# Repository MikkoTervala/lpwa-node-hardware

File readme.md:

# LPWA Node Hardware

Low power LTE Cat M / NB IoT cellular network temperature and humidity logger.

## Design Overview

The design is based on a combination of the ESP32-C3 and the SIMCom SIM7080G. An ESP32 family microcontroller was chosen as it offers good compatibility with ESPHome firmware generation tools, making the board more broadly usable for home automation purposes. In its intended use, the WiFi and Bluetooth functions will not be used. The purpose of the microcontroller is to gather temperature and humidity readings and transmit them to a server over a cellular connection using the SIM7080 modem.

## Views and Schematics

- [Schematic and board layout](https://kicanvas.org/?repo=https%3A%2F%2Fgithub.com%2FMikkoTervala%2Flpwa-node-hardware%2Ftree%2Fmain%2Fkicad)
- [Interactive 3D view](https://3dviewer.net/index.html#model=https://raw.githubusercontent.com/MikkoTervala/lpwa-node-hardware/main/kicad/release%20a/lpwa-node.step)

## Remarks

The 3.0V regulator is selected with low quiescent current as the top priority, and it cannot sustain enough current to the ESP32-C3 in WiFi operation. Replace the regulator with TLV75730PDBVR before enabling WiFi.

Maximum allowed battery voltage for the system is 4.8V. Do not use lithium 1.5V batteries as their open circuit voltage exceeds limits of this design. Stick to NiMH and alkaline.

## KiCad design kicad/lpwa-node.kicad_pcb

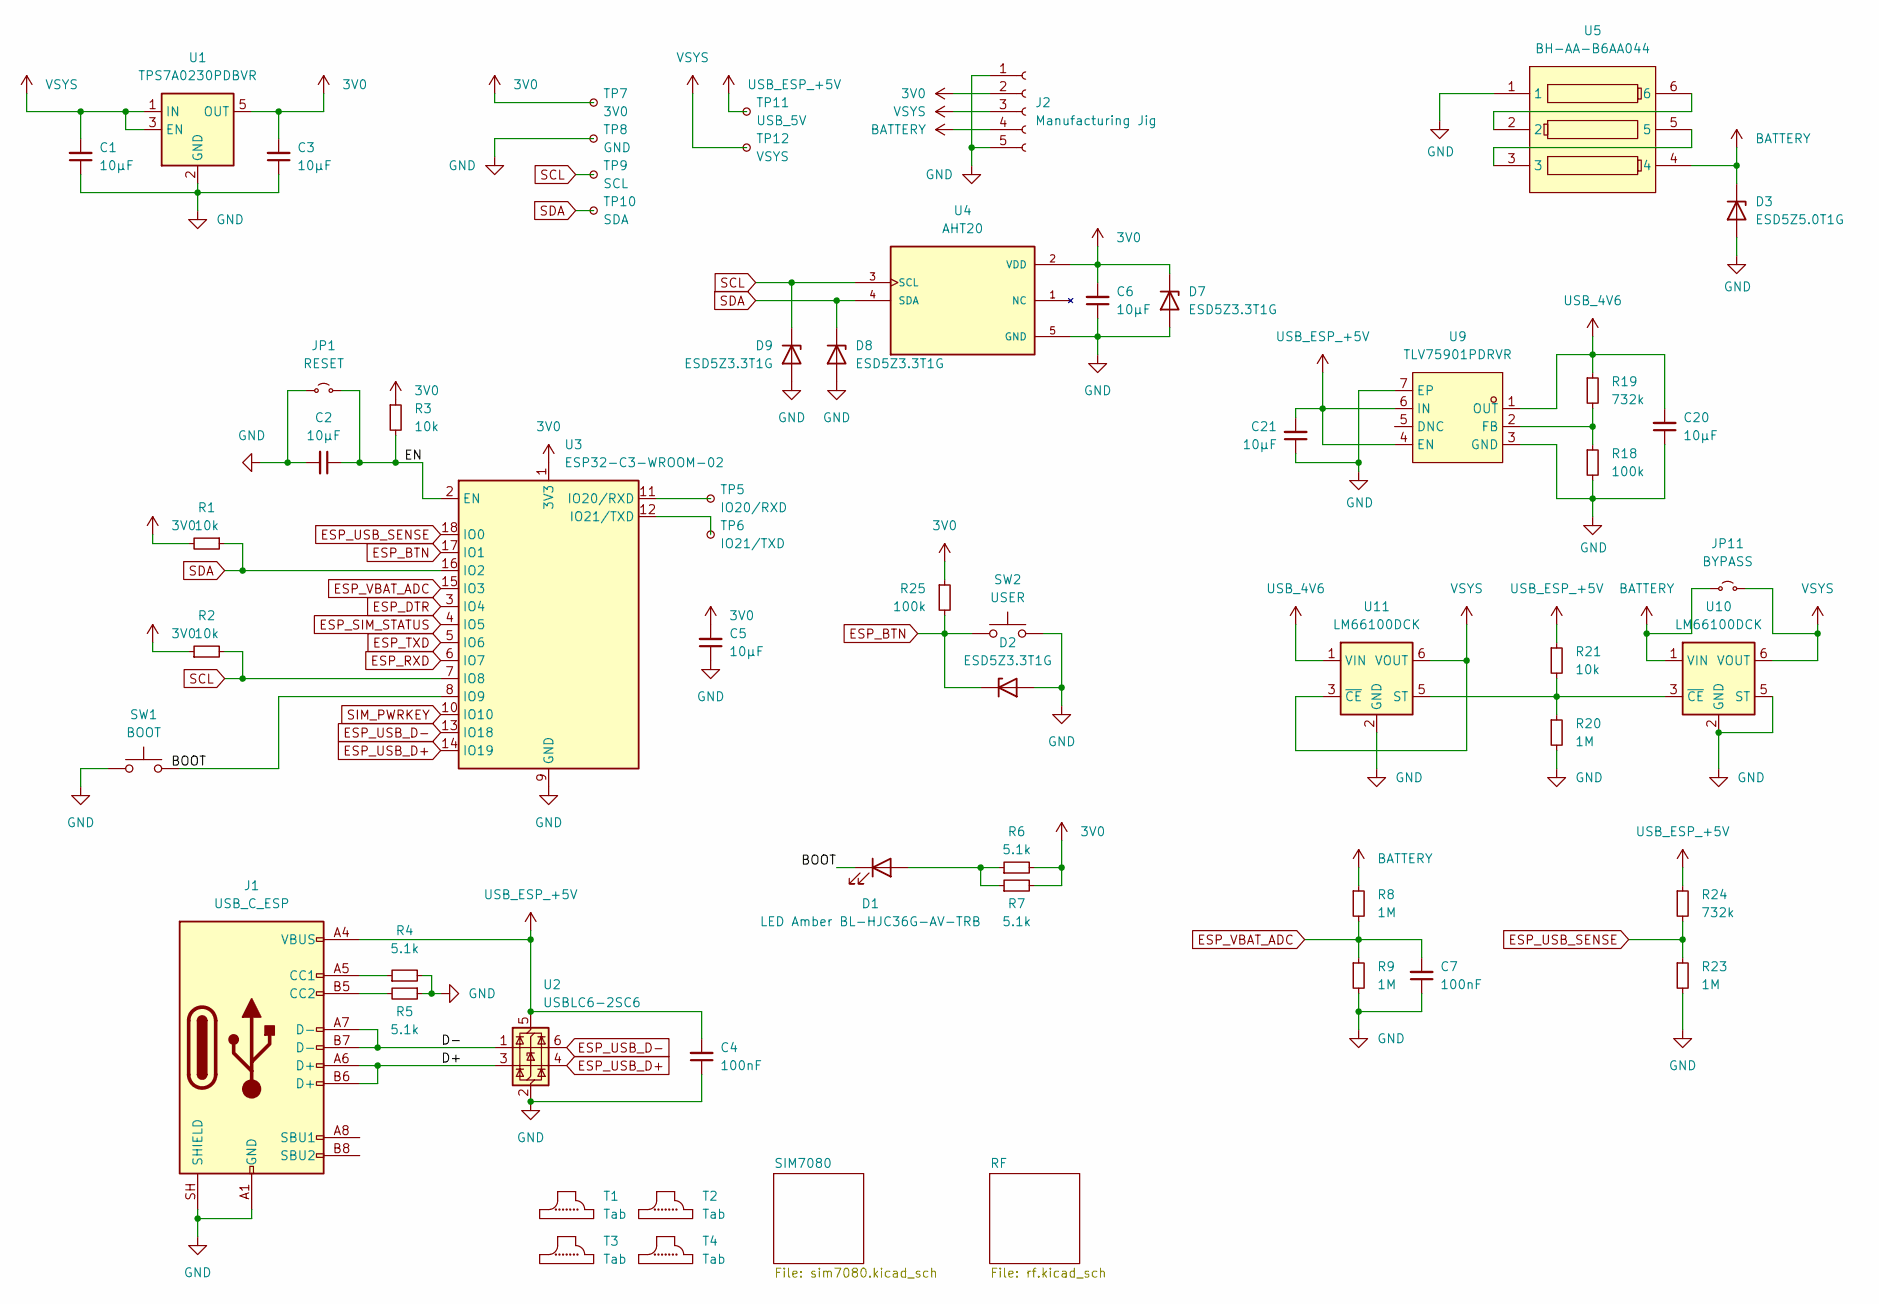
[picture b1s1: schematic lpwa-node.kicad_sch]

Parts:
C1, C2, C3, C5, C6, C20, C21: 10µF; C_0603_1608Metric; LCSC Part # C19702
C4, C7: 100nF; C_0603_1608Metric; LCSC Part # C161115
D1: LED Amber BL-HJC36G-AV-TRB; LED_0603_1608Metric; LCSC Part # C165983
D2, D7, D8, D9: ESD5Z3.3T1G; D_SOD-523; LCSC Part # C61148
D3: ESD5Z5.0T1G; D_SOD-523; LCSC Part # C82044
J1: USB_C_ESP; USB_C_Receptacle_HRO_TYPE-C-31-M-12; LCSC Part # C165948
J2: Manufacturing Jig; TestHeader_1x05_P2.54mm
JP1: RESET; SolderJumper-2_P1.3mm_Open_RoundedPad1.0x1.5mm
JP11: BYPASS; SolderJumper-2_P1.3mm_Open_RoundedPad1.0x1.5mm
R1, R2, R3, R21: 10k; R_0603_1608Metric; LCSC Part # C25804
R4, R5, R6, R7: 5.1k; R_0603_1608Metric; LCSC Part # C23186
R8, R9, R20, R23: 1M; R_0603_1608Metric; LCSC Part # C22935
R18, R25: 100k; R_0603_1608Metric; LCSC Part # C25803
R19, R24: 732k; R_0603_1608Metric; LCSC Part # C23239
SW1: BOOT; SW_Push_1P1T_XKB_TS-1187A; LCSC Part # C480267
SW2: USER; SW_Push_1P1T_XKB_TS-1187A; LCSC Part # C480267
T1, T2, T3, T4: Tab
TP5: IO20/RXD; TestPoint_Pad_D1.5mm
TP6: IO21/TXD; TestPoint_Pad_D1.5mm
TP7: 3V0; TestPoint_Pad_D1.5mm
TP8: GND; TestPoint_Pad_D1.5mm
TP9: SCL; TestPoint_Pad_D1.5mm
TP10: SDA; TestPoint_Pad_D1.5mm
TP11: USB_5V; TestPoint_Pad_D1.5mm
TP12: VSYS; TestPoint_Pad_D1.5mm
U1: TPS7A0230PDBVR; SOT-23-5; LCSC Part # C3747031
U2: USBLC6-2SC6; SOT-23-6; LCSC Part # C7519
U3: ESP32-C3-WROOM-02; LCSC Part # C2934560
U4: AHT20; PARTREV V1.0; LCSC Part # C3012622
U5: BH-AA-B6AA044; BAT-SMD_BH-AA-B6AA044; MPN BH-AA-B6AA044; LCSC Part # C19184082
U9: TLV75901PDRVR; WSON-6_L2.0-W2.0-P0.65-TL-EP; MPN TLV75901PDRVR; LCSC Part # C544759
U10, U11: LM66100DCK; SOT-363_SC-70-6; LCSC Part # C2869734

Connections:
3V0: C3.2, C5.2, C6.2, D7.1 (K), J2.2, R1.2, R2.1, R3.1, R6.2, R7.2, R25.1, TP7.1 (1_1), U1.5 (OUT), U3.1 (3V3), U4.2 (VDD); also elsewhere on the board
/BOOT: D1.1 (K), SW1.2, U3.8 (IO9)
/D+: J1.A6 (D+), J1.B6 (D+), U2.3 (I/O2)
/D-: J1.A7 (D-), J1.B7 (D-), U2.1 (I/O1)
/EN: C2.1, JP1.2 (B), R3.2, U3.2 (EN)
BATTERY: D3.1 (K), J2.4, JP11.1 (A), R8.1, U5.4, U10.1 (VIN)
ESP_BTN: D2.1 (K), R25.2, SW2.1, U3.17 (IO1)
ESP_DTR: U3.3 (IO4); also elsewhere on the board
ESP_RXD: U3.6 (IO7); also elsewhere on the board
ESP_SIM_STATUS: U3.4 (IO5); also elsewhere on the board
ESP_TXD: U3.5 (IO6); also elsewhere on the board
ESP_USB_D+: U2.4 (I/O2), U3.14 (IO19)
ESP_USB_D-: U2.6 (I/O1), U3.13 (IO18)
ESP_USB_SENSE: R23.1, R24.2, U3.18 (IO0)
ESP_VBAT_ADC: C7.2, R8.2, R9.1, U3.15 (IO3)
GND: C1.1, C2.2, C3.1, C4.1, C5.1, C6.1, C7.1, C20.1, C21.1, D2.2 (A), D3.2 (A), D7.2 (A), D8.2 (A), D9.2 (A), J1.A1 (GND), J1.A12 (GND), J1.B1 (GND), J1.B12 (GND), J1.SH (SHIELD), J2.1, J2.5, JP1.1 (A), R4.2, R5.1, R9.2, R18.2, R20.2, R23.2, SW1.1, SW2.2, TP8.1 (1_1), U1.2 (GND), U2.2 (GND), U3.9 (GND), U3.19 (GND), U4.5 (GND), U5.1, U9.3 (GND), U9.7 (EP), U10.2 (GND), U10.5 (ST), U11.2 (GND); also elsewhere on the board
unnamed: D1.2 (A), R6.1, R7.1
unnamed: J1.A5 (CC1), R4.1
unnamed: J1.B5 (CC2), R5.2
unnamed: TP5.1 (1_1), U3.11 (IO20/RXD)
unnamed: TP6.1 (1_1), U3.12 (IO21/TXD)
unnamed: U5.2, U5.6
unnamed: U5.3, U5.5
unnamed: R18.1, R19.2, U9.2 (FB)
unnamed: R20.1, R21.2, U10.3 (~CE), U11.5 (ST)
SCL: D9.1 (K), R2.2, TP9.1 (1_1), U3.7 (IO8), U4.3 (SCL)
SDA: D8.1 (K), R1.1, TP10.1 (1_1), U3.16 (IO2), U4.4 (SDA)
SIM_PWRKEY: U3.10 (IO10); also elsewhere on the board
USB_4V6: C20.2, R19.1, U9.1 (OUT), U11.1 (VIN)
USB_ESP_+5V: C4.2, C21.2, J1.A4 (VBUS), J1.A9 (VBUS), J1.B4 (VBUS), J1.B9 (VBUS), R21.1, R24.1, TP11.1 (1_1), U2.5 (VBUS), U9.4 (EN), U9.6 (IN)
VSYS: C1.2, J2.3, JP11.2 (B), TP12.1 (1_1), U1.1 (IN), U1.3 (EN), U10.6 (VOUT), U11.3 (~CE), U11.6 (VOUT); also elsewhere on the board

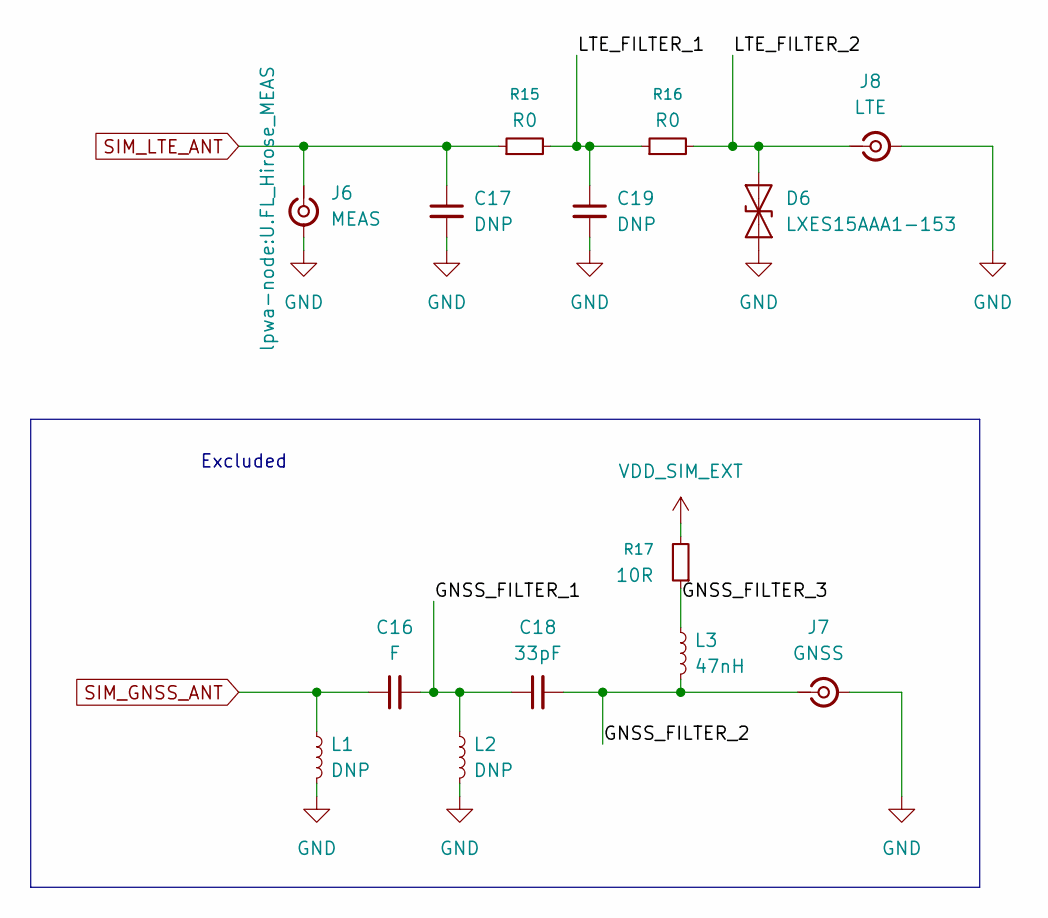
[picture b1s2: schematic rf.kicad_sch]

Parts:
C16: F; C_0402_1005Metric
C17, C19: DNP; C_0402_1005Metric
C18: 33pF; C_0402_1005Metric
D6: LXES15AAA1-153; D_SOD-882; LCSC Part # C7472903
J6: MEAS; U.FL_Hirose_MEAS; LCSC Part # C88374
J7: GNSS; U.FL_Hirose_U.FL-R-SMT-1_Vertical; LCSC Part # C88374
J8: LTE; U.FL_Hirose_U.FL-R-SMT-1_Vertical; LCSC Part # C88374
L1, L2: DNP; L_0402_1005Metric
L3: 47nH; L_0402_1005Metric
R15, R16: R0; R_0402_1005Metric; LCSC Part # C60485
R17: 10R; R_0402_1005Metric

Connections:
/RF/LTE_FILTER_1: C19.1, R15.2, R16.1
/RF/LTE_FILTER_2: D6.2 (A2), J8.1 (In), R16.2
GND: C17.2, C19.2, D6.1 (A1), J6.2 (Ext), J7.2 (Ext), J8.2 (Ext), L1.2, L2.2; also elsewhere on the board
unnamed: C16.1, L1.1
unnamed: C16.2, C18.1, L2.1
unnamed: C18.2, J7.1 (In), L3.2
unnamed: L3.1, R17.1
SIM_LTE_ANT: C17.1, J6.1 (In), R15.1; also elsewhere on the board

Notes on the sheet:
Excluded

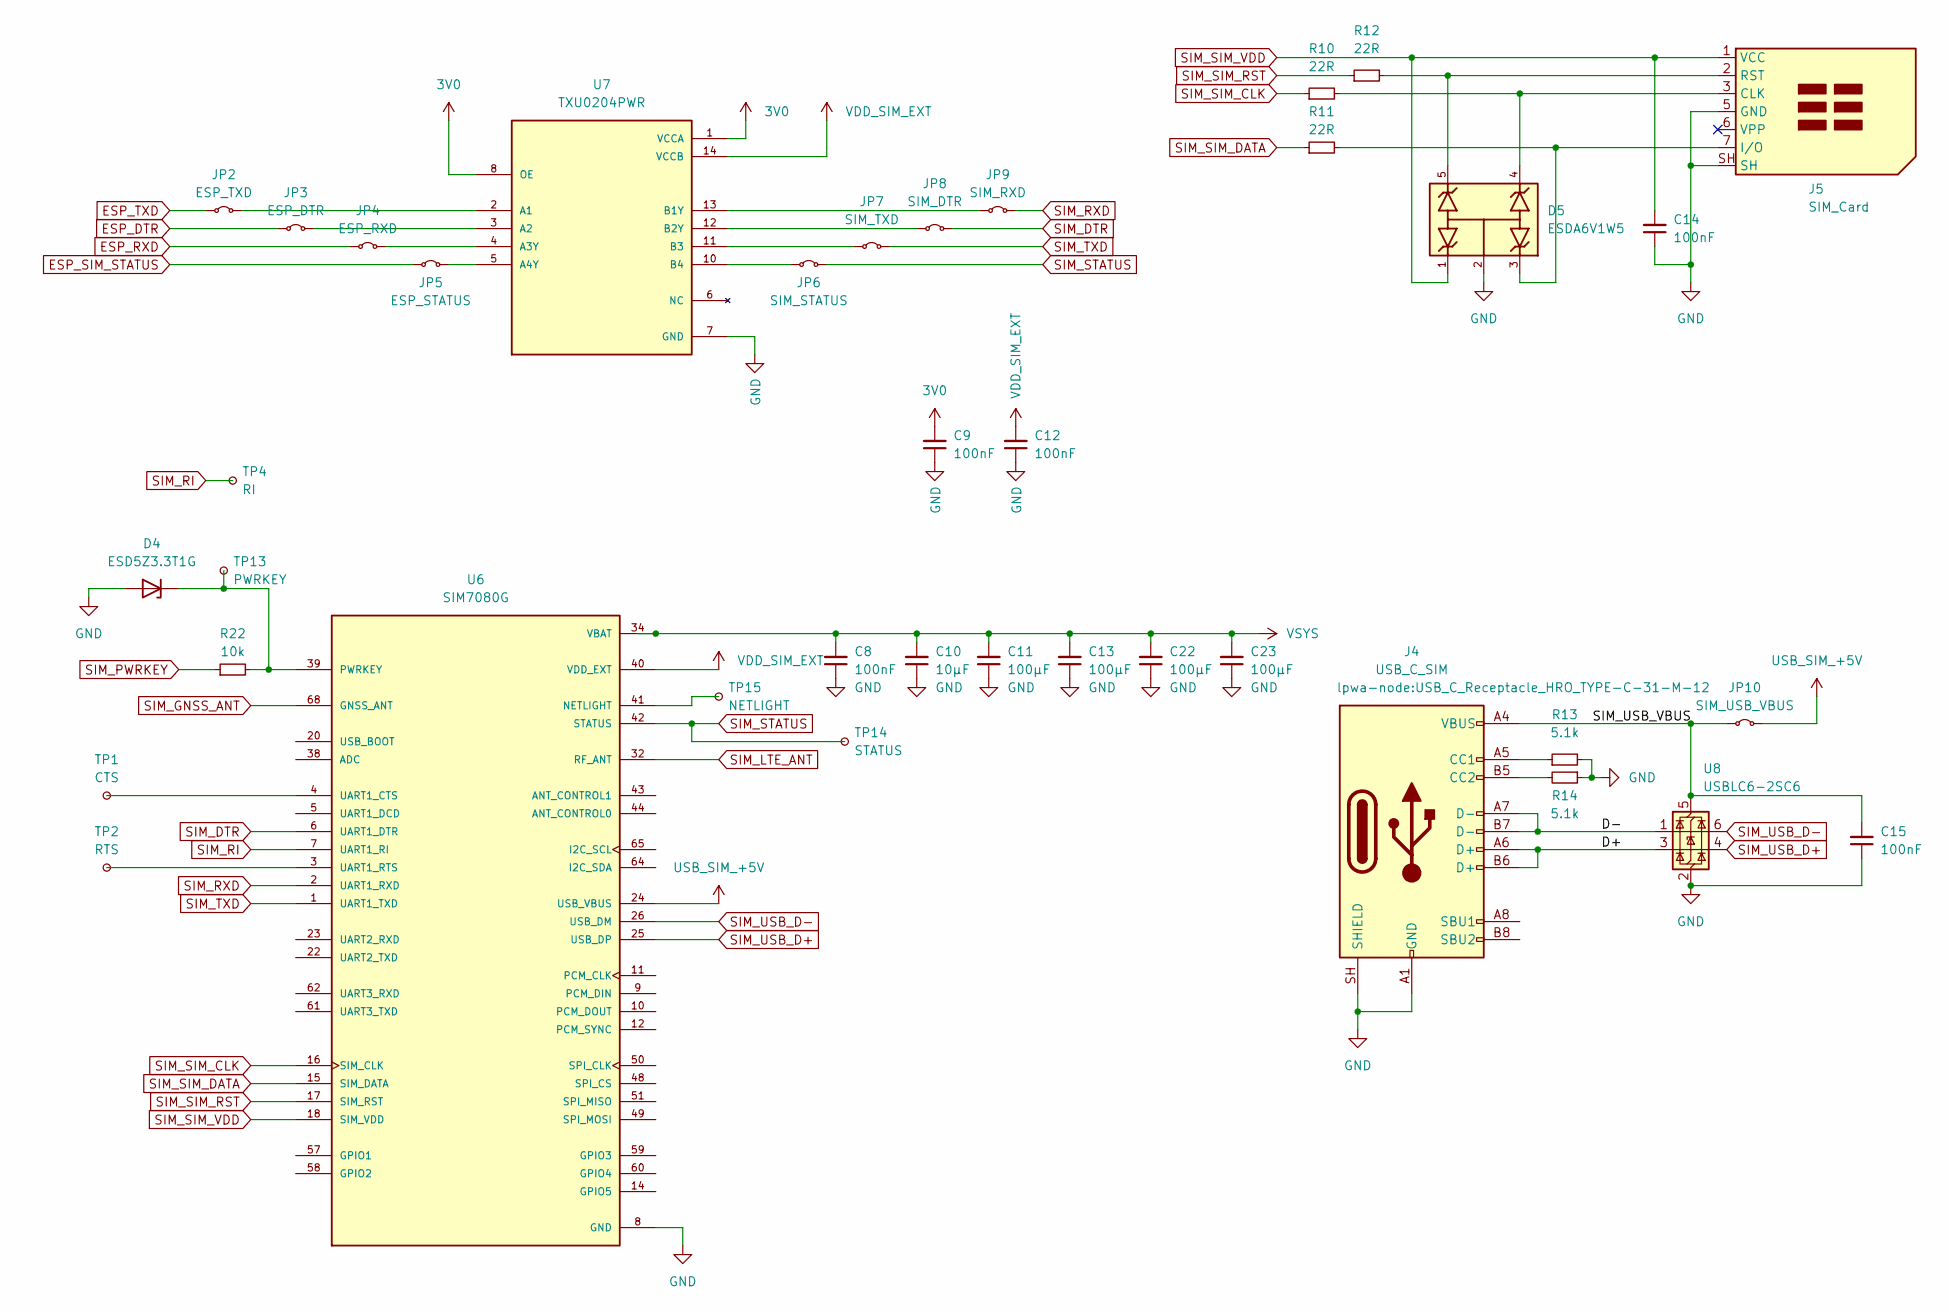
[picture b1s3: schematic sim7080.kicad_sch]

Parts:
C8, C9, C12, C14, C15: 100nF; C_0603_1608Metric; LCSC Part # C161115
C10: 10µF; C_0603_1608Metric; LCSC Part # C19702
C11, C13, C22, C23: 100µF; C_1206_3216Metric; LCSC Part # C7432784
D4: ESD5Z3.3T1G; D_SOD-523; LCSC Part # C61148
D5: ESDA6V1W5; SOT65P210X110-5N; PARTREV 2; LCSC Part # C48677
J4: USB_C_SIM; USB_C_Receptacle_HRO_TYPE-C-31-M-12; LCSC Part # C165948
J5: SIM_Card; SMN-304; LCSC Part # C266889
JP2: ESP_TXD; SolderJumper-2_P1.3mm_Bridged_RoundedPad1.0x1.5mm
JP3: ESP_DTR; SolderJumper-2_P1.3mm_Bridged_RoundedPad1.0x1.5mm
JP4: ESP_RXD; SolderJumper-2_P1.3mm_Bridged_RoundedPad1.0x1.5mm
JP5: ESP_STATUS; SolderJumper-2_P1.3mm_Bridged_RoundedPad1.0x1.5mm
JP6: SIM_STATUS; SolderJumper-2_P1.3mm_Bridged_RoundedPad1.0x1.5mm
JP7: SIM_TXD; SolderJumper-2_P1.3mm_Bridged_RoundedPad1.0x1.5mm
JP8: SIM_DTR; SolderJumper-2_P1.3mm_Bridged_RoundedPad1.0x1.5mm
JP9: SIM_RXD; SolderJumper-2_P1.3mm_Bridged_RoundedPad1.0x1.5mm
JP10: SIM_USB_VBUS; SolderJumper-2_P1.3mm_Bridged_RoundedPad1.0x1.5mm
R10, R11, R12: 22R; R_0603_1608Metric; LCSC Part # C23345
R13, R14: 5.1k; R_0603_1608Metric; LCSC Part # C23186
R22: 10k; R_0603_1608Metric; LCSC Part # C25804
TP1: CTS; TestPoint_Pad_D1.5mm
TP2: RTS; TestPoint_Pad_D1.5mm
TP4: RI; TestPoint_Pad_D1.5mm
TP13: PWRKEY; TestPoint_Pad_D1.5mm
TP14: STATUS; TestPoint_Pad_D1.5mm
TP15: NETLIGHT; TestPoint_Pad_D1.5mm
U6: SIM7080G; PARTREV 1.04; LCSC Part # C18548266
U7: TXU0204PWR; SOP65P640X120-14N; PARTREV A; LCSC Part # C4363888
U8: USBLC6-2SC6; SOT-23-6; LCSC Part # C7519

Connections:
3V0: C9.2, U7.1 (VCCA), U7.8 (OE); also elsewhere on the board
/SIM7080/D+: J4.A6 (D+), J4.B6 (D+), U8.3 (I/O2)
/SIM7080/D-: J4.A7 (D-), J4.B7 (D-), U8.1 (I/O1)
/SIM7080/SIM_USB_VBUS: C15.2, J4.A4 (VBUS), J4.A9 (VBUS), J4.B4 (VBUS), J4.B9 (VBUS), JP10.1 (A), U8.5 (VBUS)
ESP_DTR: JP3.1 (A); also elsewhere on the board
ESP_RXD: JP4.1 (A); also elsewhere on the board
ESP_SIM_STATUS: JP5.1 (A); also elsewhere on the board
ESP_TXD: JP2.1 (A); also elsewhere on the board
GND: C8.1, C9.1, C10.1, C11.1, C12.1, C13.1, C14.1, C15.1, C22.1, C23.1, D4.2 (A), D5.2, J4.A1 (GND), J4.A12 (GND), J4.B1 (GND), J4.B12 (GND), J4.SH (SHIELD), J5.5 (GND), J5.SH, R13.2, R14.1, U6.8 (GND), U6.13 (GND), U6.19 (GND), U6.21 (GND), U6.27 (GND), U6.30 (GND), U6.31 (GND), U6.33 (GND), U6.36 (GND), U6.37 (GND), U6.45 (GND), U6.63 (GND), U6.66 (GND), U6.67 (GND), U6.69 (GND), U6.70 (GND), U6.71 (GND), U6.72 (GND), U6.73 (GND), U6.74 (GND), U6.75 (GND), U6.76 (GND), U6.77 (GND), U7.7 (GND), U8.2 (GND); also elsewhere on the board
unnamed: D4.1 (K), R22.2, TP13.1 (1_1), U6.39 (PWRKEY)
unnamed: J4.A5 (CC1), R13.1
unnamed: J4.B5 (CC2), R14.2
unnamed: D5.4, J5.3 (CLK), R10.2
unnamed: D5.3, J5.7 (I/O), R11.2
unnamed: D5.5, J5.2 (RST), R12.2
unnamed: JP2.2 (B), U7.2 (A1)
unnamed: JP3.2 (B), U7.3 (A2)
unnamed: JP4.2 (B), U7.4 (A3Y)
unnamed: JP5.2 (B), U7.5 (A4Y)
unnamed: JP6.1 (A), U7.10 (B4)
unnamed: JP7.1 (A), U7.11 (B3)
unnamed: JP8.1 (A), U7.12 (B2Y)
unnamed: JP9.1 (A), U7.13 (B1Y)
unnamed: TP15.1 (1_1), U6.41 (NETLIGHT)
unnamed: TP1.1 (1_1), U6.4 (UART1_CTS)
unnamed: TP2.1 (1_1), U6.3 (UART1_RTS)
SIM_DTR: JP8.2 (B), U6.6 (UART1_DTR)
SIM_GNSS_ANT: U6.68 (GNSS_ANT)
SIM_LTE_ANT: U6.32 (RF_ANT); also elsewhere on the board
SIM_PWRKEY: R22.1; also elsewhere on the board
SIM_RI: TP4.1 (1_1), U6.7 (UART1_RI)
SIM_RXD: JP9.2 (B), U6.2 (UART1_RXD)
SIM_SIM_CLK: R10.1, U6.16 (SIM_CLK)
SIM_SIM_DATA: R11.1, U6.15 (SIM_DATA)
SIM_SIM_RST: R12.1, U6.17 (SIM_RST)
SIM_SIM_VDD: C14.2, D5.1, J5.1 (VCC), U6.18 (SIM_VDD)
SIM_STATUS: JP6.2 (B), TP14.1 (1_1), U6.42 (STATUS)
SIM_TXD: JP7.2 (B), U6.1 (UART1_TXD)
SIM_USB_D+: U6.25 (USB_DP), U8.4 (I/O2)
SIM_USB_D-: U6.26 (USB_DM), U8.6 (I/O1)
USB_SIM_+5V: JP10.2 (B), U6.24 (USB_VBUS)
VDD_SIM_EXT: C12.2, U6.40 (VDD_EXT), U7.14 (VCCB)
VSYS: C8.2, C10.2, C11.2, C13.2, C22.2, C23.2, U6.34 (VBAT), U6.35 (VBAT); also elsewhere on the board

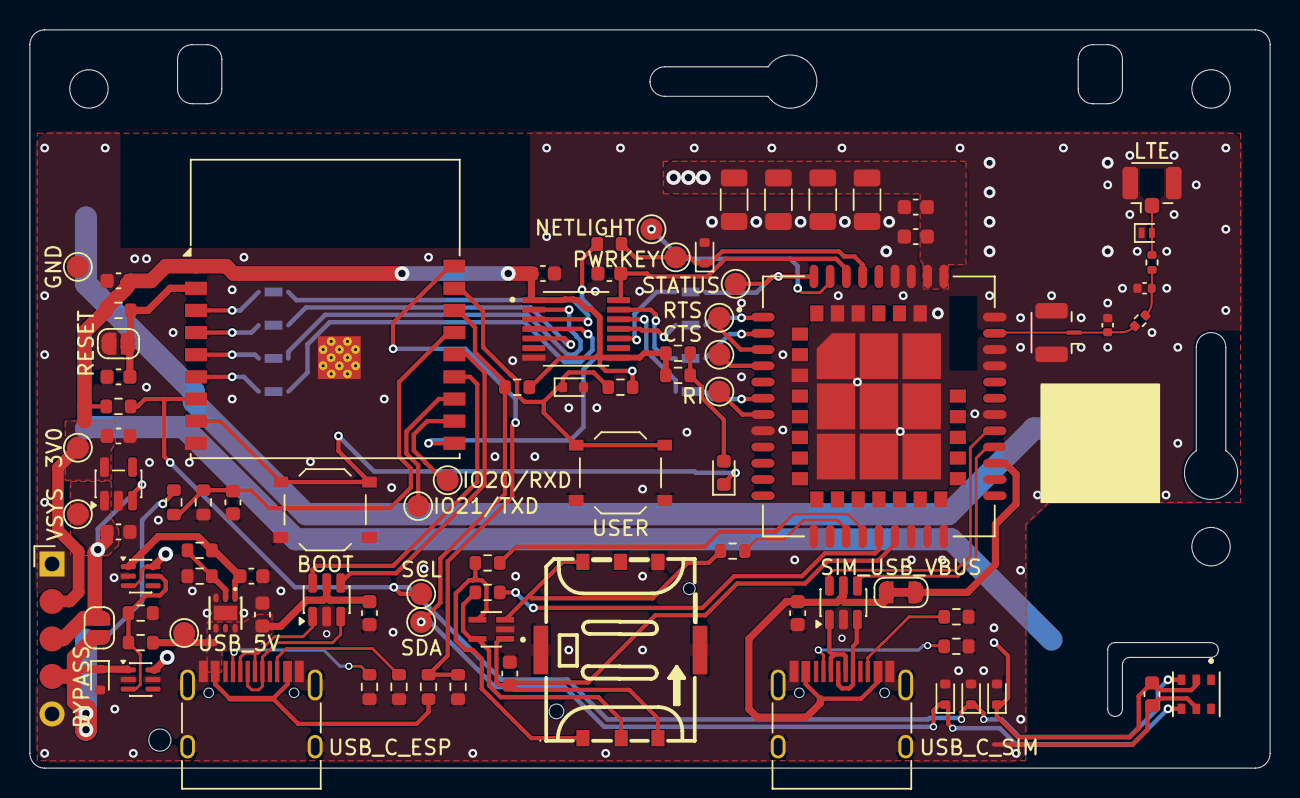
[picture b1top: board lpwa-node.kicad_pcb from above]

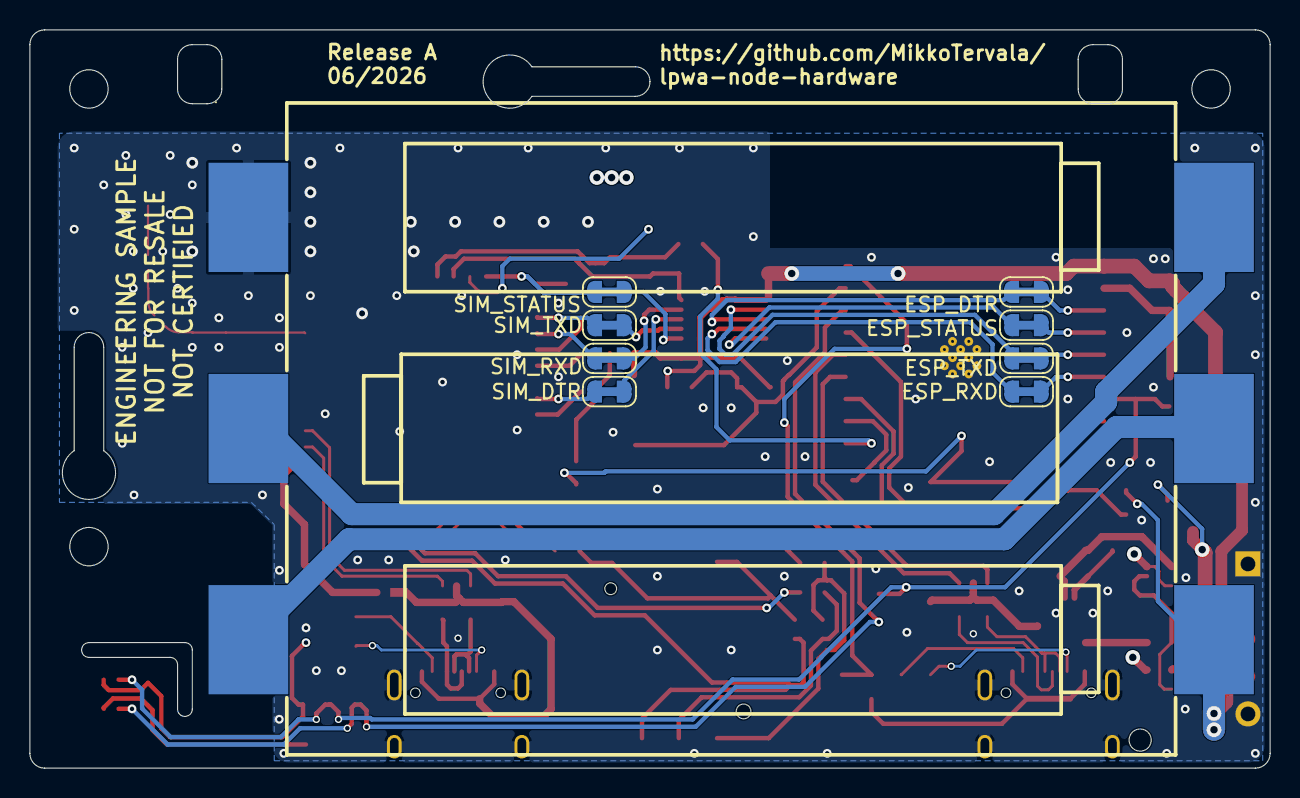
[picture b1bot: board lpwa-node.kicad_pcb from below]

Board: 4 copper layers, 84.0 x 50.0 mm, 102 parts (9 on the bottom side), 67 nets.

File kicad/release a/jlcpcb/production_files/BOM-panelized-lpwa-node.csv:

Comment,Designator,Footprint,LCSC,Quantity
100k,"R18,R25",R_0603_1608Metric,C25803,2
100nF,"C12,C14,C15,C4,C7,C8,C9",C_0603_1608Metric,C161115,7
100µF,"C11,C13,C22,C23",C_1206_3216Metric,C7432784,4
10k,"R1,R2,R21,R22,R3",R_0603_1608Metric,C25804,5
10µF,"C1,C10,C2,C20,C21,C3,C5,C6",C_0603_1608Metric,C19702,8
1M,"R20,R23,R8,R9",R_0603_1608Metric,C22935,4
22R,"R10,R11,R12",R_0603_1608Metric,C23345,3
5.1k,"R13,R14,R4,R5,R6,R7",R_0603_1608Metric,C23186,6
732k,"R19,R24",R_0603_1608Metric,C23239,2
AHT20,U4,AHT20,C3012622,1
BH-AA-B6AA044,U5,BAT-SMD_BH-AA-B6AA044,C19184082,1
BOOT,SW1,SW_Push_1P1T_XKB_TS-1187A,C480267,1
ESD5Z3.3T1G,"D2,D4,D7,D8,D9",D_SOD-523,C61148,5
ESD5Z5.0T1G,D3,D_SOD-523,C82044,1
ESDA6V1W5,D5,SOT65P210X110-5N,C48677,1
ESP32-C3-WROOM-02,U3,ESP32-C3-WROOM-02,C2934560,1
LED Amber BL-HJC36G-AV-TRB,D1,LED_0603_1608Metric,C165983,1
LM66100DCK,"U10,U11",SOT-363_SC-70-6,C2869734,2
LTE,J8,U.FL_Hirose_U.FL-R-SMT-1_Vertical,C88374,1
LXES15AAA1-153,D6,D_SOD-882,C7472903,1
R0,"R15,R16",R_0402_1005Metric,C60485,2
SIM7080G,U6,SIM7080G,C18548266,1
SIM_Card,J5,SMN-304,C266889,1
TLV75901PDRVR,U9,WSON-6_L2.0-W2.0-P0.65-TL-EP,C544759,1
TPS7A0230PDBVR,U1,SOT-23-5,C3747031,1
TXU0204PWR,U7,SOP65P640X120-14N,C4363888,1
USBLC6-2SC6,"U2,U8",SOT-23-6,C7519,2
USB_C_ESP,J1,USB_C_Receptacle_HRO_TYPE-C-31-M-12,C165948,1
USER,SW2,SW_Push_1P1T_XKB_TS-1187A,C480267,1

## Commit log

2026-05-31 Add licence
2026-06-01 Add component symbols and footprints
2026-06-01 Add 3d model
2026-06-01 Draft
2026-06-02 Add components to libraries
2026-06-05 Remove copper from mechanical holes
2026-06-05 First orderable version
2026-06-07 Optimize for manufacturing, add part numbers
2026-06-07 Add modified project specific headers
2026-06-08 Release A
2026-06-08 Add readme
